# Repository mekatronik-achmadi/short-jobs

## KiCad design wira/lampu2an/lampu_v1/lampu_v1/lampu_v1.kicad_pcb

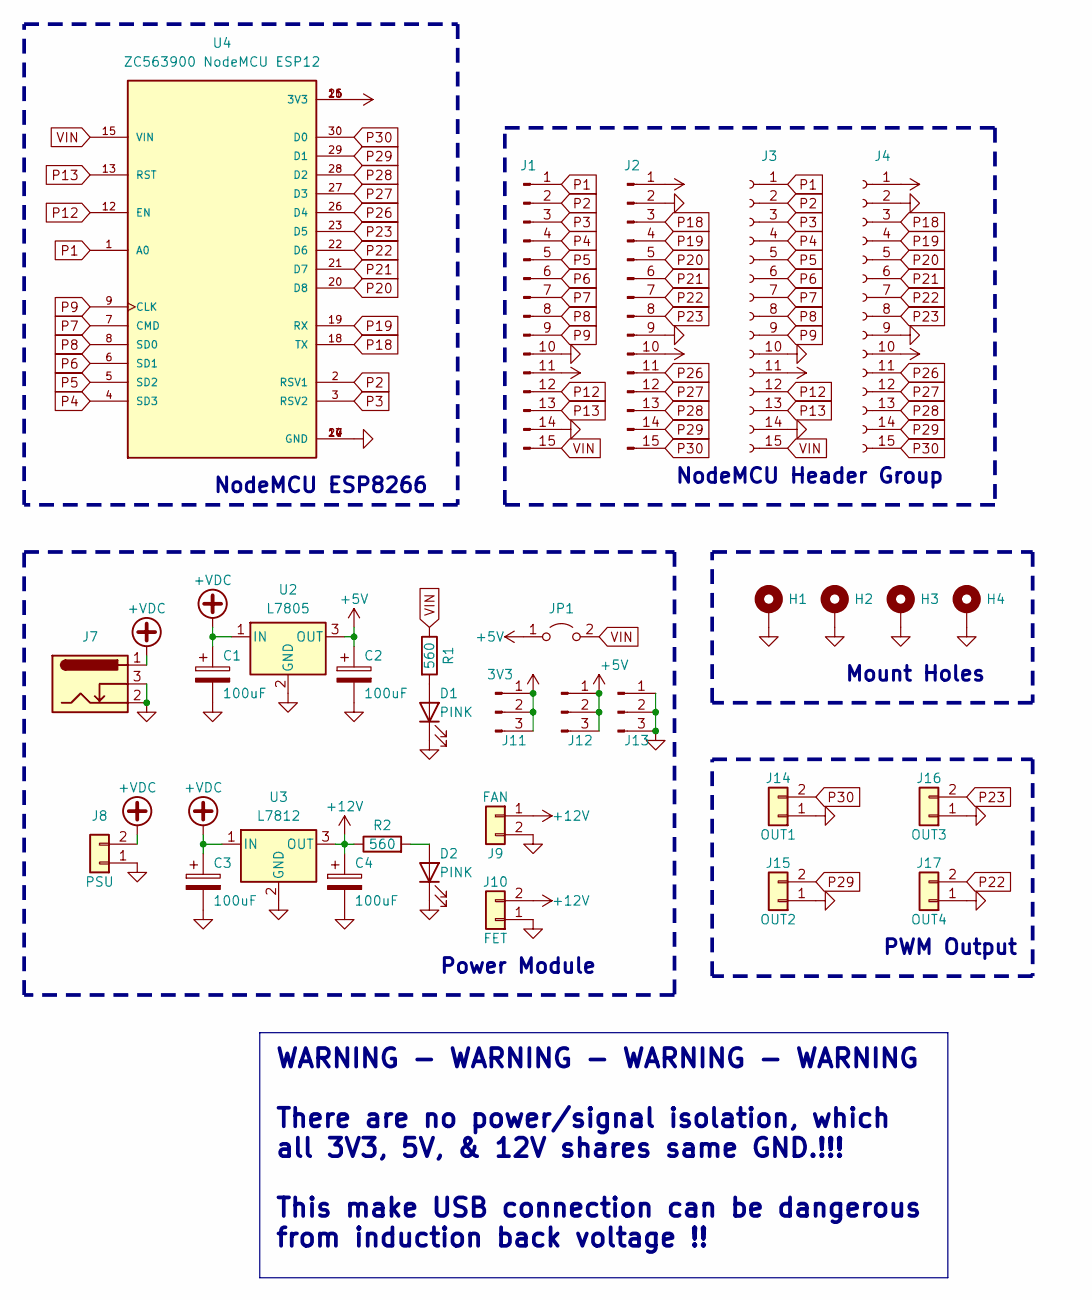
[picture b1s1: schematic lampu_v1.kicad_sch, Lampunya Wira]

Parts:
C1, C2, C3, C4: 100uF; CP_Radial_D5.0mm_P2.50mm
D1, D2: PINK; LED_D3.0mm
H1, H2, H3, H4: MountingHole_Pad; MountingHole_2.5mm_Pad
J1, J2: Conn_01x15_Pin; PinHeader_1x15_P2.54mm_Vertical
J3, J4: Conn_01x15_Socket; PinSocket_1x15_P2.54mm_Vertical
J7: Barrel_Jack_Switch; BarrelJack_Horizontal
J8: PSU; TerminalBlock_Altech_AK300-2_P5.00mm
J9: FAN; JST_XH_B2B-XH-A_1x02_P2.50mm_Vertical
J10: FET; TerminalBlock_Altech_AK300-2_P5.00mm
J11: 3V3; PinHeader_1x03_P2.54mm_Vertical
J12: 5V; PinHeader_1x03_P2.54mm_Vertical
J13: GND; PinHeader_1x03_P2.54mm_Vertical
J14: OUT1; TerminalBlock_Altech_AK300-2_P5.00mm
J15: OUT2; TerminalBlock_Altech_AK300-2_P5.00mm
J16: OUT3; TerminalBlock_Altech_AK300-2_P5.00mm
J17: OUT4; TerminalBlock_Altech_AK300-2_P5.00mm
JP1: Jumper_2_Open; SolderJumper-2_P1.3mm_Open_RoundedPad1.0x1.5mm
R1, R2: 560; R_Axial_DIN0207_L6.3mm_D2.5mm_P7.62mm_Horizontal
U2: L7805; TO-220F-3_Vertical
U3: L7812; TO-220F-3_Vertical
U4: ZC563900 NodeMCU ESP12; MODULE_ZC563900; PARTREV 1.0

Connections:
+5V: C2.1, J12.1, J12.2, J12.3, JP1.1 (A), U2.3 (OUT)
+12V: C4.1, J9.1, J10.2, R2.1, U3.3 (OUT)
+VDC: C1.1, C3.1, J7.1, J8.2, U2.1 (IN), U3.1 (IN)
GND: C1.2, C2.2, C3.2, C4.2, D1.1 (K), D2.1 (K), H1.1, H2.1, H3.1, H4.1, J1.10, J1.14, J2.2, J2.9, J3.10, J3.14, J4.2, J4.9, J7.2, J7.3, J8.1, J9.2, J10.1, J13.1, J13.2, J13.3, J14.1, J15.1, J16.1, J17.1, U2.2 (GND), U3.2 (GND), U4.10 (GND), U4.14 (GND), U4.17 (GND), U4.24 (GND)
unnamed: D1.2 (A), R1.2
unnamed: D2.2 (A), R2.2
P1: J1.1, J3.1, U4.1 (A0)
P2: J1.2, J3.2, U4.2 (RSV1)
P3: J1.3, J3.3, U4.3 (RSV2)
P4: J1.4, J3.4, U4.4 (SD3)
P5: J1.5, J3.5, U4.5 (SD2)
P6: J1.6, J3.6, U4.6 (SD1)
P7: J1.7, J3.7, U4.7 (CMD)
P8: J1.8, J3.8, U4.8 (SD0)
P9: J1.9, J3.9, U4.9 (CLK)
P12: J1.12, J3.12, U4.12 (EN)
P13: J1.13, J3.13, U4.13 (RST)
P18: J2.3, J4.3, U4.18 (TX)
P19: J2.4, J4.4, U4.19 (RX)
P20: J2.5, J4.5, U4.20 (D8)
P21: J2.6, J4.6, U4.21 (D7)
P22: J2.7, J4.7, J17.2, U4.22 (D6)
P23: J2.8, J4.8, J16.2, U4.23 (D5)
P26: J2.11, J4.11, U4.26 (D4)
P27: J2.12, J4.12, U4.27 (D3)
P28: J2.13, J4.13, U4.28 (D2)
P29: J2.14, J4.14, J15.2, U4.29 (D1)
P30: J2.15, J4.15, J14.2, U4.30 (D0)
VDD: J1.11, J2.1, J2.10, J3.11, J4.1, J4.10, J11.1, J11.2, J11.3, U4.11 (3V3), U4.16 (3V3), U4.25 (3V3)
VIN: J1.15, J3.15, JP1.2 (B), R1.1, U4.15 (VIN)

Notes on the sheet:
WARNING - WARNING - WARNING - WARNING There are no power/signal isolation, which all 3V3, 5V, & 12V shares same GND.!!! This make USB connection can be dangerous from induction back voltage !!
NodeMCU Header Group
Mount Holes
NodeMCU ESP8266
PWM Output
Power Module

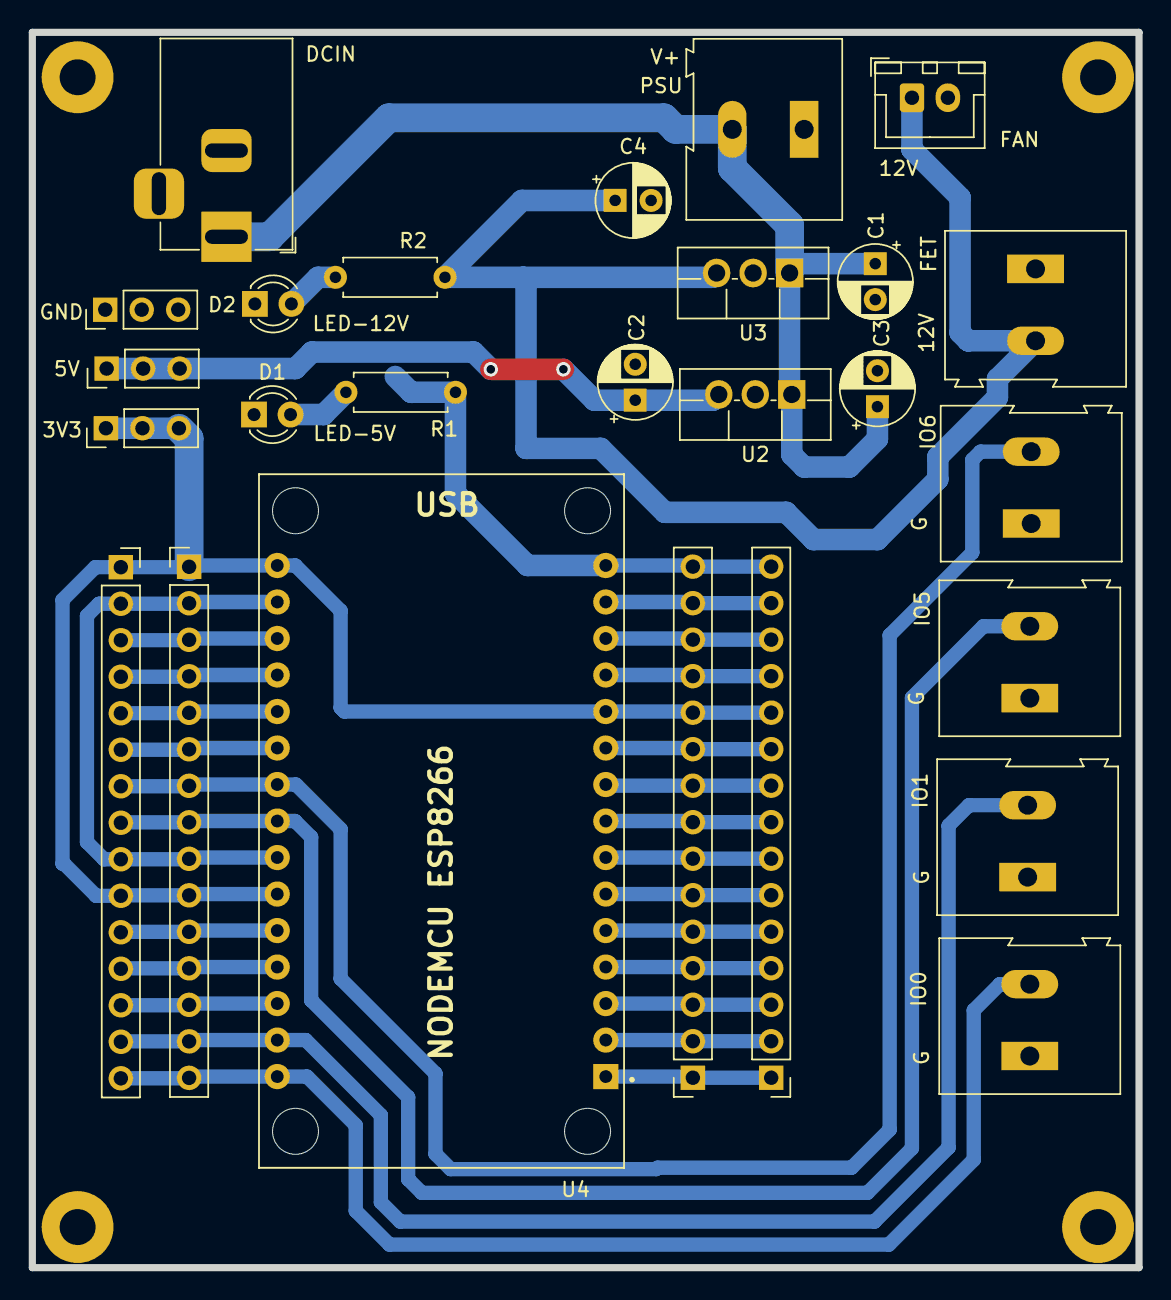
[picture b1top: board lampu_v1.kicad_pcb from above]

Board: 2 copper layers, 77.0 x 86.0 mm, 31 parts (1 on the bottom side), 30 nets.

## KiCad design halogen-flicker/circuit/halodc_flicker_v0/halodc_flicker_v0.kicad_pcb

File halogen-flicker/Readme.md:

# DC Halogen Flicker

A small circuit to help create flicker using Halogen based lamp. 
Using a MOSFET and ATTiny chip to control the the negative side of Lamp.

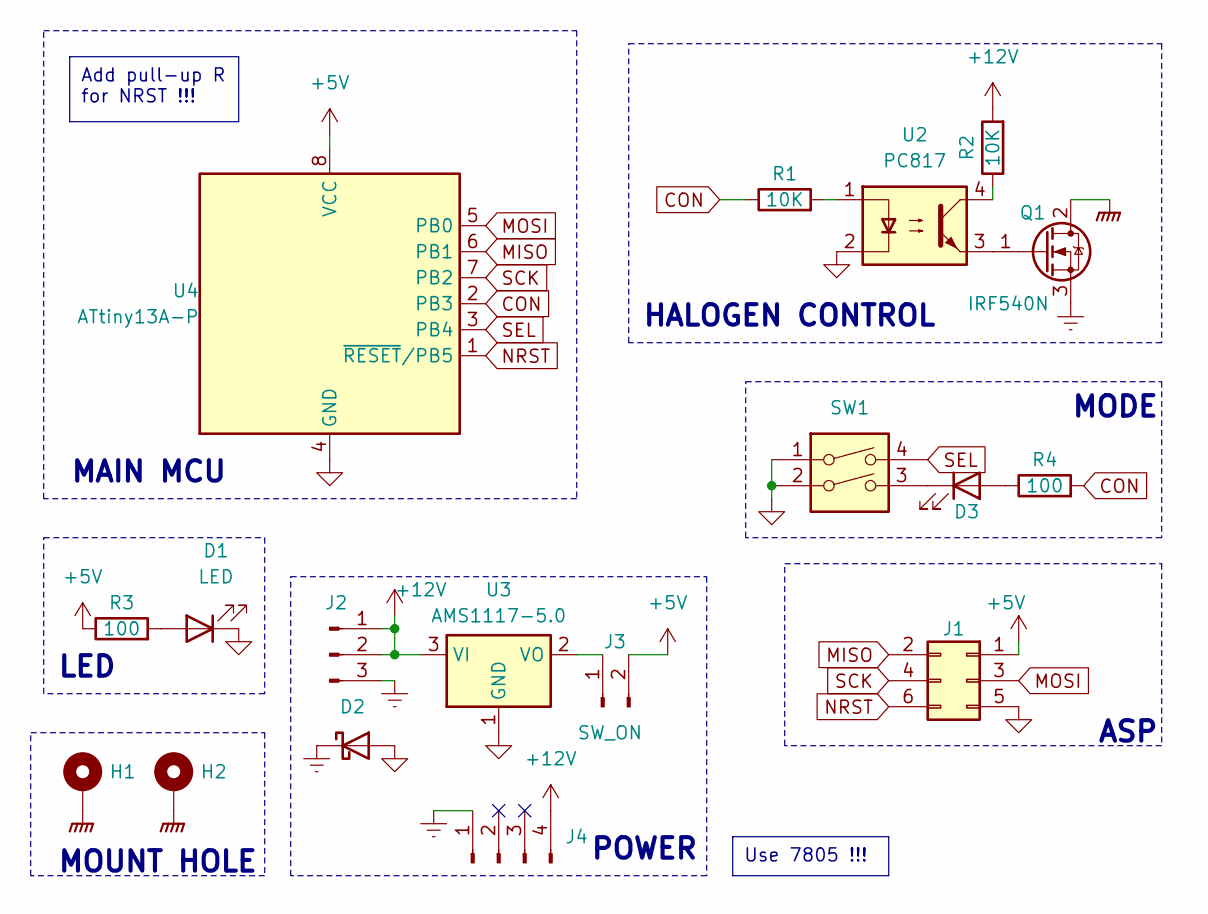
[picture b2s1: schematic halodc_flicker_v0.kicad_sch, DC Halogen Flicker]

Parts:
D1, D3: LED; LED_0805_2012Metric_Pad1.15x1.40mm_HandSolder
D2: D_Schottky; D_SMA-SMB_Universal_Handsoldering
H1, H2: MountingHole_Pad; MountingHole_4.5mm_Pad
J1: ASP; PinHeader_2x03_P2.54mm_Vertical
J2: BATT_LAMP; TerminalBlock_Altech_AK300-3_P5.00mm
J3: SW_ON; PinSocket_1x02_P2.54mm_Vertical
J4: CHARGER; Molex_KK-254_AE-6410-04A_1x04_P2.54mm_Vertical
Q1: IRF540N; TO-220-3_Horizontal_TabDown
R1, R2: 10K; R_0805_2012Metric_Pad1.20x1.40mm_HandSolder
R3, R4: 100; R_0805_2012Metric_Pad1.20x1.40mm_HandSolder
SW1: SW_DIP_x02; SW_DIP_SPSTx02_Slide_9.78x7.26mm_W7.62mm_P2.54mm
U2: PC817; DIP-4_W7.62mm
U3: AMS1117-5.0; SOT-223-3_TabPin2
U4: ATtiny13A-P; DIP-8_W7.62mm

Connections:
+5V: J1.1, J3.2, R3.1, U4.8 (VCC)
+12V: J2.1, J2.2, J4.4, R2.2, U3.3 (VI)
CON: R1.1, R4.2, U4.2 (PB3)
GND: D1.1 (K), D2.2 (A), J1.5, SW1.1, SW1.2, U2.2, U3.1 (GND), U4.4 (GND)
GNDPWR: H1.1, H2.1, Q1.2 (D)
GNDREF: D2.1 (K), J2.3, J4.1, Q1.3 (S)
MISO: J1.2, U4.6 (PB1)
MOSI: J1.3, U4.5 (PB0)
NRST: J1.6, U4.1 (~RESET/PB5)
unnamed: D1.2 (A), R3.2
unnamed: D3.2 (A), R4.1
unnamed: D3.1 (K), SW1.3
unnamed: J3.1, U3.2 (VO)
unnamed: Q1.1 (G), U2.3
unnamed: R1.2, U2.1
unnamed: R2.1, U2.4
SCK: J1.4, U4.7 (PB2)
SEL: SW1.4, U4.3 (PB4)

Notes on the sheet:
Use 7805 !!!
Add pull-up R for NRST !!!
HALOGEN CONTROL
MAIN MCU
POWER
MODE
ASP
MOUNT HOLE
LED

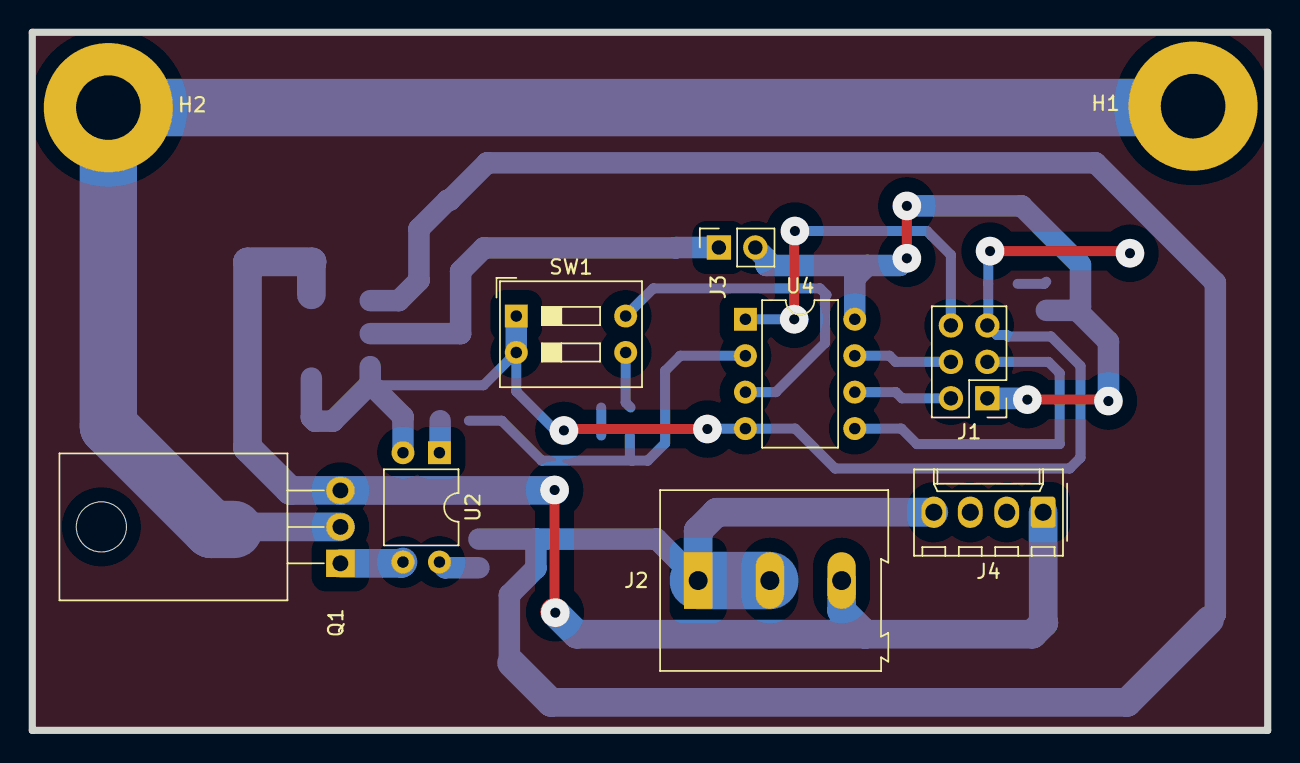
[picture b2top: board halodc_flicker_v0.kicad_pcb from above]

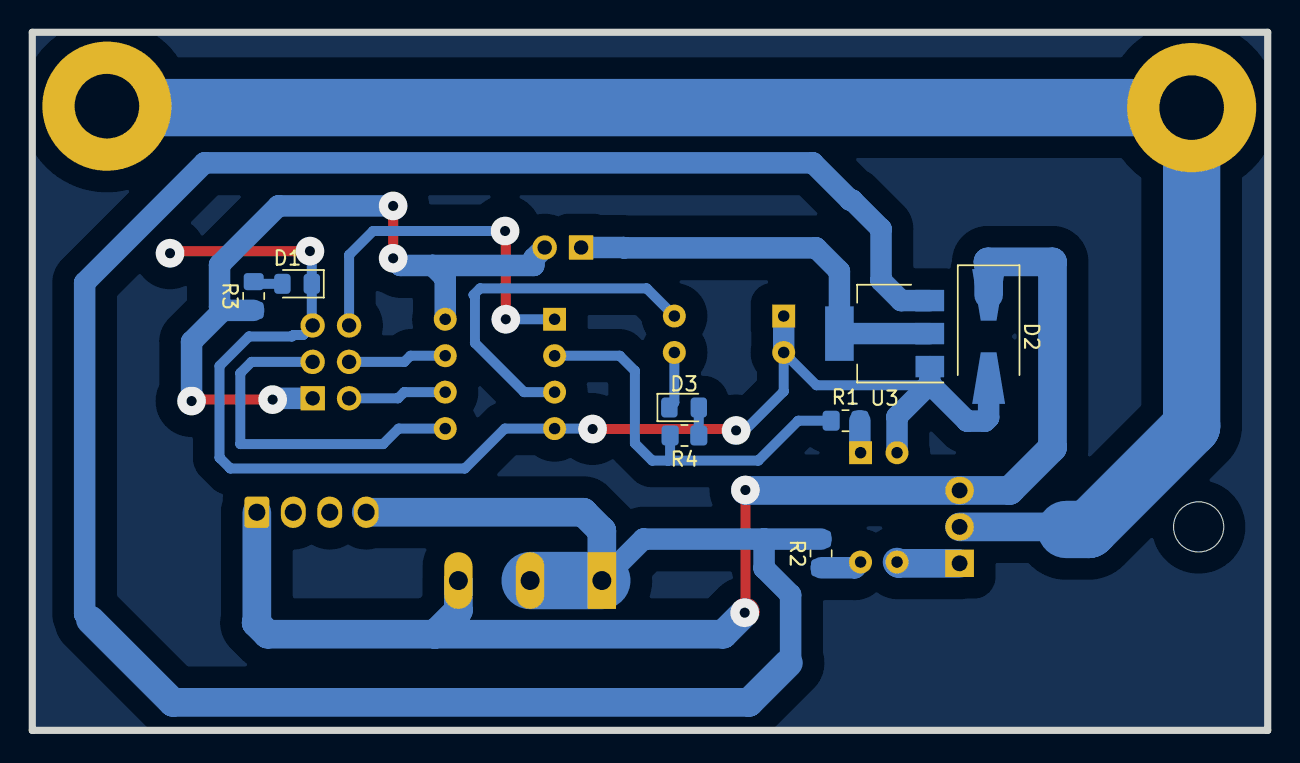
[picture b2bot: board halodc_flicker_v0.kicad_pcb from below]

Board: 2 copper layers, 86.1 x 48.6 mm, 18 parts (8 on the bottom side), 18 nets.

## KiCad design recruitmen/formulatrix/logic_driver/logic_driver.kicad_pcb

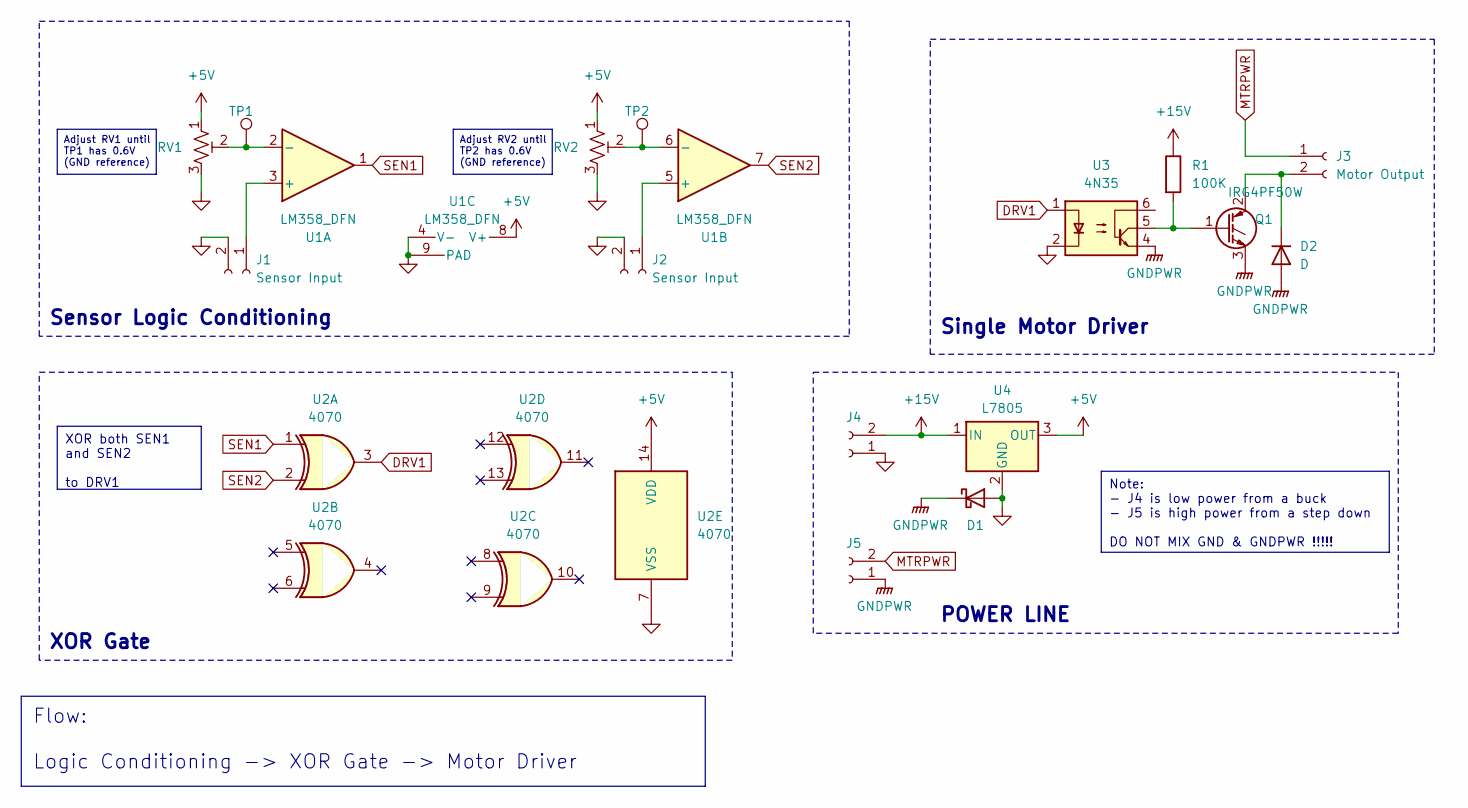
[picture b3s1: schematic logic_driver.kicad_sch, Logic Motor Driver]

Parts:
D1: D_Schottky; D_A-405_P7.62mm_Horizontal
D2: D; D_A-405_P7.62mm_Horizontal
J1, J2: Sensor Input; TerminalBlock_Altech_AK300-2_P5.00mm
J3: Motor Output; TerminalBlock_Altech_AK300-2_P5.00mm
J4, J5: Conn_01x02_Socket; TerminalBlock_Altech_AK300-2_P5.00mm
Q1: IRG4PF50W; TO-247-3_Vertical
R1: 100K; R_1206_3216Metric_Pad1.30x1.75mm_HandSolder
RV1, RV2: R_Potentiometer_Trim_US; Potentiometer_Vishay_T73YP_Vertical
TP1, TP2: TestPoint; TestPoint_Pad_D4.0mm
U1: LM358_DFN; DFN-8-1EP_2x2mm_P0.5mm_EP1.05x1.75mm
U2: 4070; DIP-14_W8.89mm_SMDSocket_LongPads
U3: 4N35; DIP-6_W7.62mm
U4: L7805; TO-252-2

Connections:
+5V: RV1.1, RV2.1, U1.8 (V+), U2.14 (VDD), U4.3 (OUT)
+15V: J4.2, R1.1, U4.1 (IN)
DRV1: U2.3, U3.1
GND: D1.2 (A), J1.2, J2.2, J4.1, RV1.3, RV2.3, U1.4 (V-), U1.9 (PAD), U2.7 (VSS), U3.2, U4.2 (GND)
GNDPWR: D1.1 (K), D2.2 (A), J5.1, Q1.3 (E), U3.4
MTRPWR: J3.1, J5.2
unnamed: D2.1 (K), J3.2, Q1.2 (C)
unnamed: J1.1, U1.3 (+)
unnamed: J2.1, U1.5 (+)
unnamed: Q1.1 (G), R1.2, U3.5
unnamed: RV1.2, TP1.1, U1.2 (-)
unnamed: RV2.2, TP2.1, U1.6 (-)
SEN1: U1.1, U2.1
SEN2: U1.7, U2.2

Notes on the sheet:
Adjust RV1 until TP1 has 0.6V (GND reference)
XOR both SEN1 and SEN2 to DRV1
Adjust RV2 until TP2 has 0.6V (GND reference)
Flow: Logic Conditioning -> XOR Gate -> Motor Driver
Note: - J4 is low power from a buck - J5 is high power from a step down DO NOT MIX GND & GNDPWR !!!!!
Single Motor Driver
Sensor Logic Conditioning
XOR Gate
POWER LINE

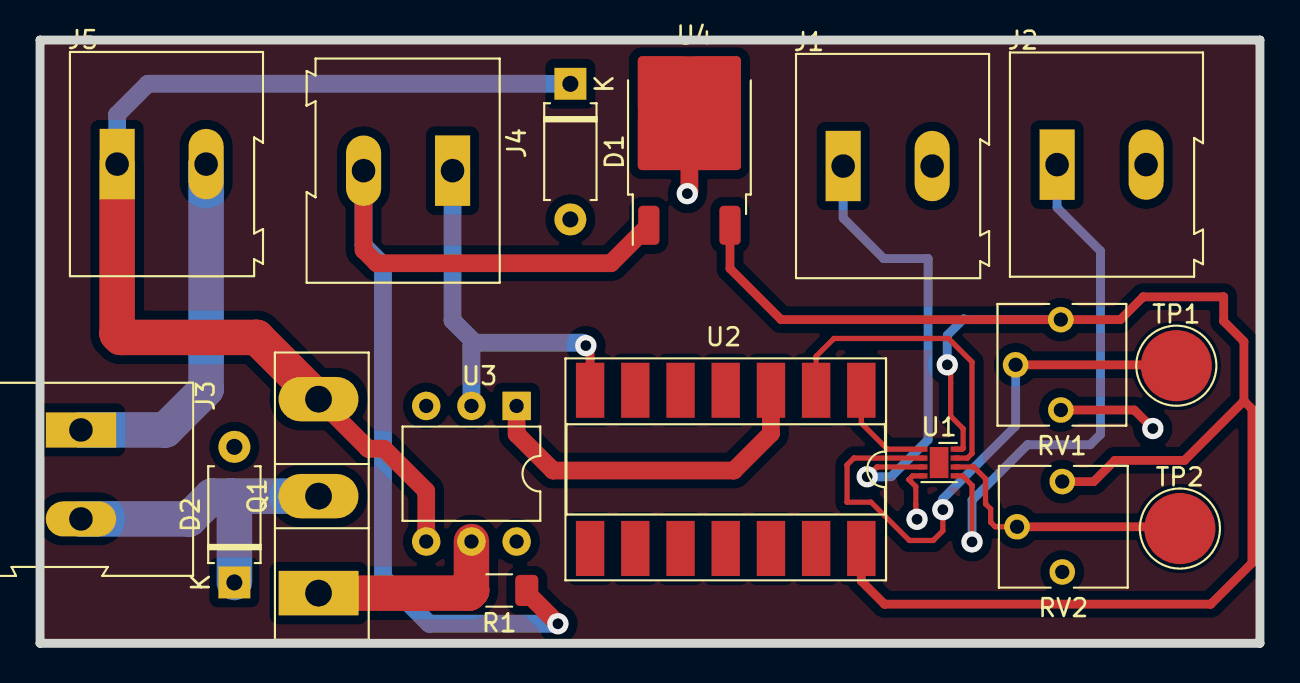
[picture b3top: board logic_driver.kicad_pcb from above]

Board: 2 copper layers, 68.5 x 33.9 mm, 17 parts (0 on the bottom side), 14 nets.

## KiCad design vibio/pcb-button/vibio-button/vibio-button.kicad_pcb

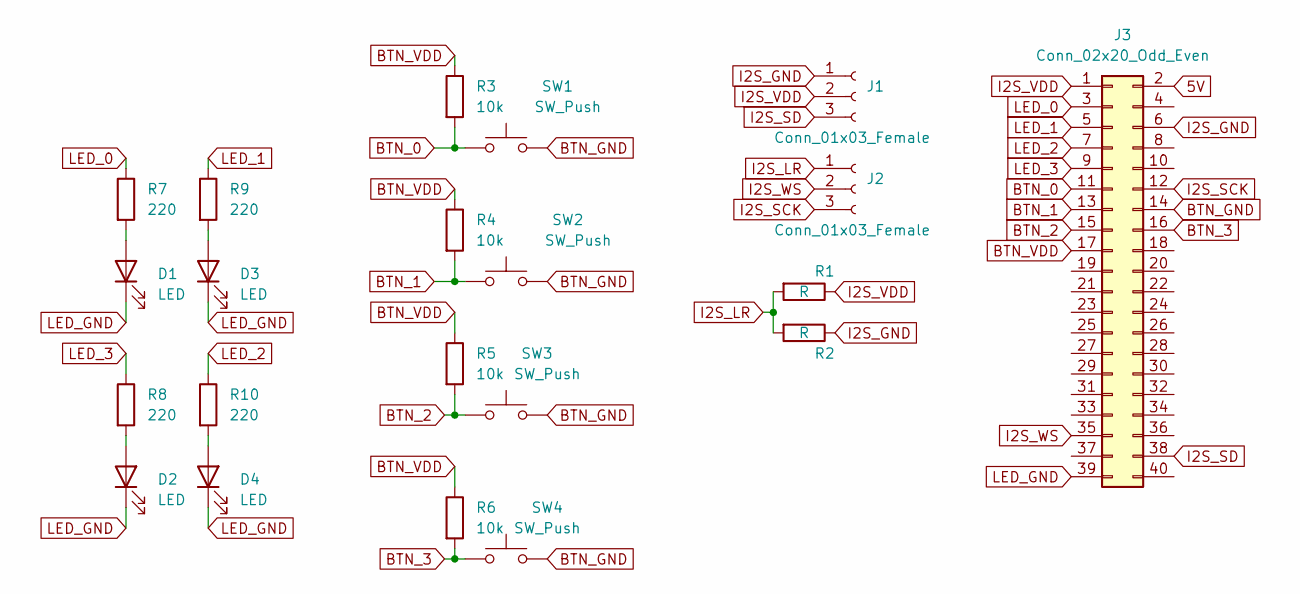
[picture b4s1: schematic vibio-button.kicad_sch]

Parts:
D1, D2, D3, D4: LED; LED_1206_3216Metric_Pad1.42x1.75mm_HandSolder
J1, J2: Conn_01x03_Female; PinSocket_1x03_P2.54mm_Vertical
J3: Conn_02x20_Odd_Even; PinSocket_2x20_P2.54mm_Vertical
R1, R2: R; R_0805_2012Metric_Pad1.20x1.40mm_HandSolder
R3, R4, R5, R6: 10k; R_0805_2012Metric_Pad1.20x1.40mm_HandSolder
R7, R8, R9, R10: 220; R_0805_2012Metric_Pad1.20x1.40mm_HandSolder
SW1, SW2, SW3, SW4: SW_Push; SW_PUSH-12mm

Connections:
5V: J3.2
BTN_0: J3.11, R3.2, SW1.1
BTN_1: J3.13, R4.2, SW2.1
BTN_2: J3.15, R5.2, SW3.1
BTN_3: J3.16, R6.2, SW4.1
BTN_GND: J3.14, SW1.2, SW2.2, SW3.2, SW4.2
BTN_VDD: J3.17, R3.1, R4.1, R5.1, R6.1
I2S_GND: J1.1, J3.6, R2.1
I2S_LR: J2.1, R1.2, R2.2
I2S_SCK: J2.3, J3.12
I2S_SD: J1.3, J3.38
I2S_VDD: J1.2, J3.1, R1.1
I2S_WS: J2.2, J3.35
LED_0: J3.3, R7.1
LED_1: J3.5, R9.1
LED_2: J3.7, R10.1
LED_3: J3.9, R8.1
LED_GND: D1.1 (K), D2.1 (K), D3.1 (K), D4.1 (K), J3.39
unnamed: D1.2 (A), R7.2
unnamed: D2.2 (A), R8.2
unnamed: D3.2 (A), R9.2
unnamed: D4.2 (A), R10.2

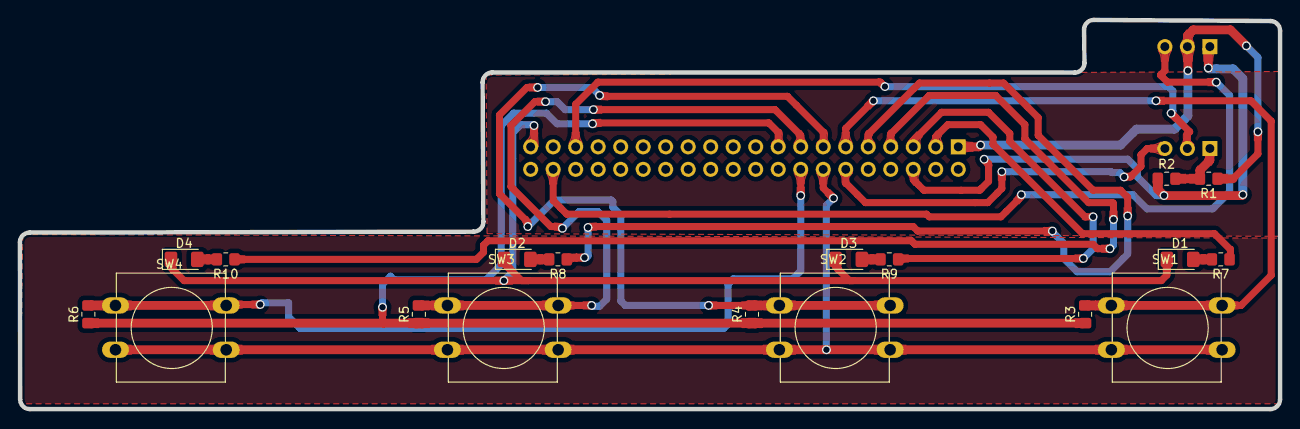
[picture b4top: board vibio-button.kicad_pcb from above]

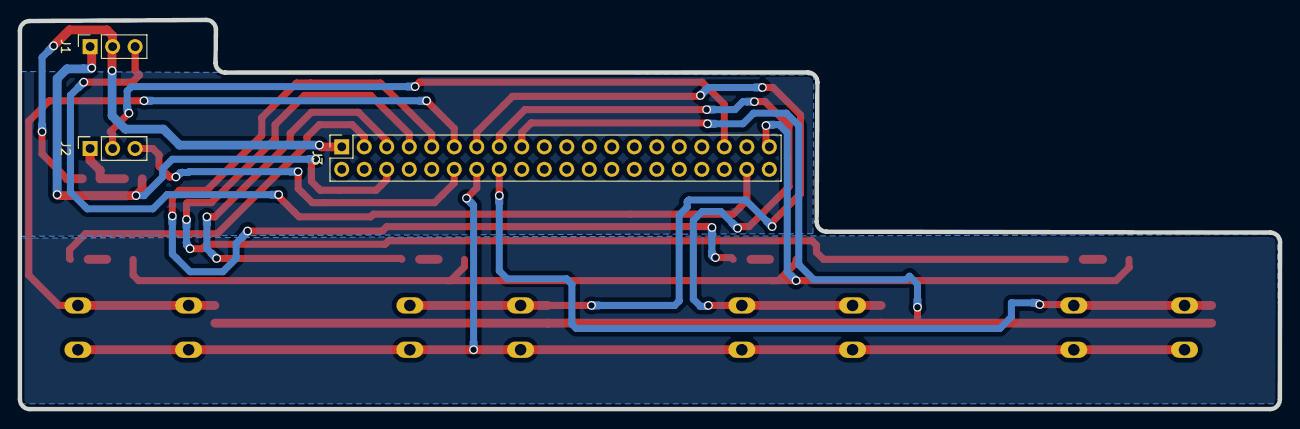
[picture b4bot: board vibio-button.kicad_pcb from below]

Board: 2 copper layers, 142.2 x 43.9 mm, 21 parts (3 on the bottom side), 21 nets.

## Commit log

2022-11-28 Vibio PCB Initial Commit
2022-12-01 Vibio Button PCB
2022-12-02 Start Vibio Document Design
2022-12-02 Vibio 3D
2022-12-04 Vibio oh Vibio
2022-12-04 Plan Vibio
2022-12-06 OpenPLC
2022-12-06 OpenPLC Runtime
2022-12-06 OpenPLC Editor
2022-12-06 OpenPLC editor failed on Python3
2022-12-06 OpenPLC run editor
2022-12-06 Need more time to test the editor
2022-12-28 redesign PCB
2022-12-28 Ready to Order
2023-01-05 Tasklist
2024-07-04 PCB Recruitment
2024-07-12 DC Halogen Flicker
2024-07-12 Halogen FLicker
2024-07-16 Update PCB FLicker Halogen
2024-07-16 Update PCB FLicker
2024-07-25 Halogen and ATTiny is hard
2024-07-26 Halogen Control is On
2024-08-06 PCB ne Wira
2024-08-07 Update Lampu Wira
2024-08-07 Wira PCB
2024-08-08 Lampunya Wira
2024-08-15 Wiring Lampunya Wira
